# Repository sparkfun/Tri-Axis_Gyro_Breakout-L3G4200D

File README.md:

SparkFun Tri-Axis Gyro Breakout - L3G4200D
========================================

[*SparkFun Tri-Axis Gyro Breakout - L3G4200D (SEN-10612)*](https://www.sparkfun.com/products/10612)

This is a breakout board for the L3G4200D low-power three-axis angular rate sensor. 
The L3G4200D is a MEMS motion sensor and has a full scale of ±250/±500/±2000 dps and is capable of measuring rates with a user-selectable bandwidth. 

Repository Contents
-------------------

* **/Firmware** - Example code 
* **/Hardware** - Eagle design files (.brd, .sch)
* **/Production** - Production panel files (.brd)

Documentation
--------------
* **[SparkFun Fritzing repo](https://github.com/sparkfun/Fritzing_Parts)** - Fritzing diagrams for SparkFun products.
* **[SparkFun 3D Model repo](https://github.com/sparkfun/3D_Models)** - 3D models of SparkFun products. 

License Information
-------------------
This product is _**open source**_! 

The **hardware** is released under [Creative Commons ShareAlike 4.0 International](https://creativecommons.org/licenses/by-sa/4.0/).

The **code** is beerware; if you see me (or any other SparkFun employee) at the local, and you've found our code helpful, please buy us a round!

Please use, reuse, and modify these files as you see fit. Please maintain attribution to SparkFun Electronics and release anything derivative under the same license.

Distributed as-is; no warranty is given.

- Your friends at SparkFun.

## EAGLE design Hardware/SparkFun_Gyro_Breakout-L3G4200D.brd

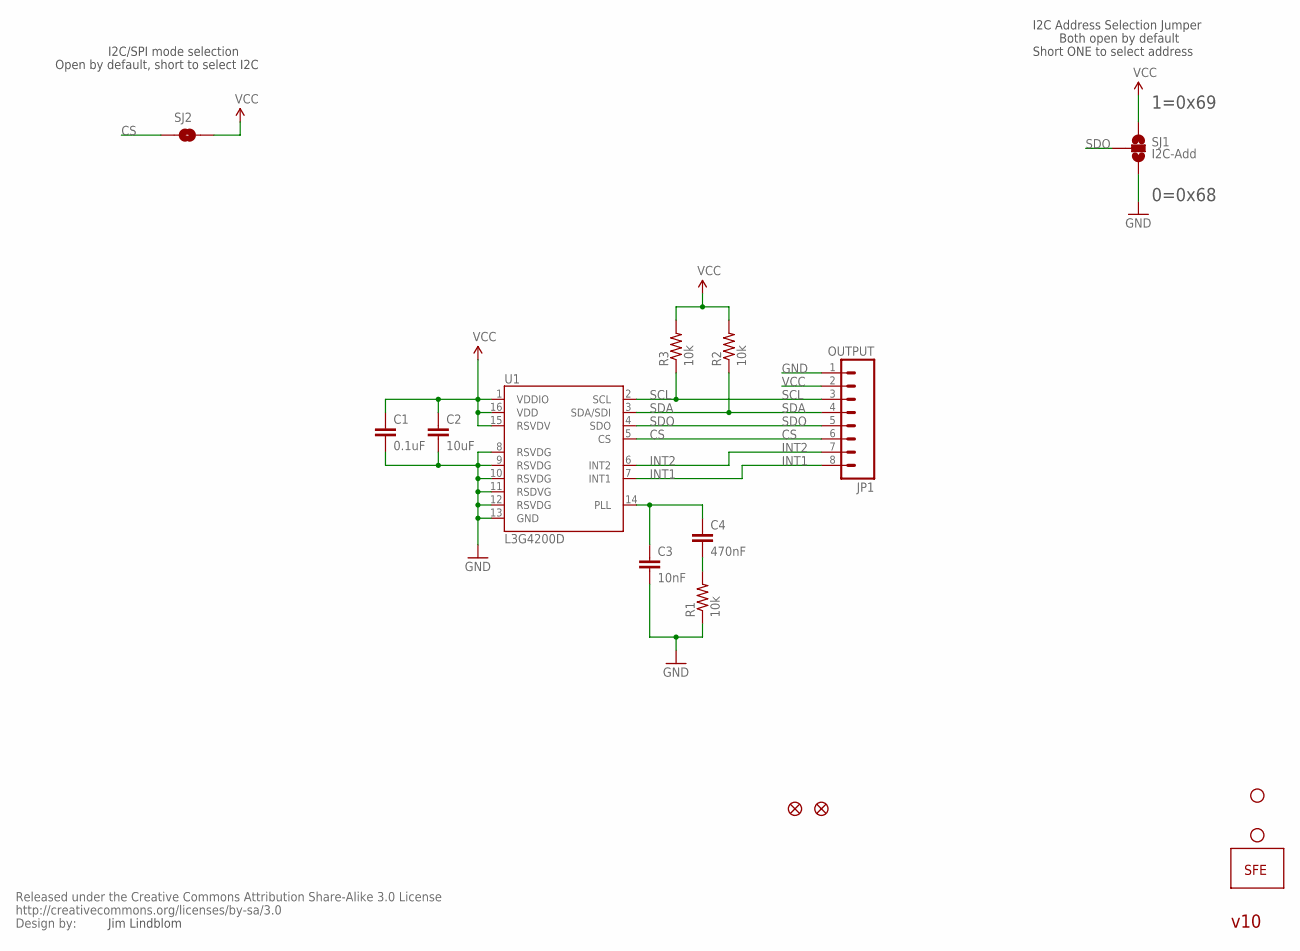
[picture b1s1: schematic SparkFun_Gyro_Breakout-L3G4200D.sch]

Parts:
C1: 0.1uF; 0402-CAP
C2: 10uF; 1206
C3: 10nF; 0402-CAP
C4: 470nF; 0402-CAP
JP1: OUTPUT; 1X08
JP2, JP3: STAND-OFF
JP4: LOGO-SFESK; SFE-LOGO-FLAME
JP5, JP6: FIDUCIAL1X2; FIDUCIAL-1X2
R1, R2, R3: 10k; 0402-RES
SJ1: I2C-Add; SJ_3
SJ2: I2C-Mode; SJ_2S-NO
U1: L3G4200D; LGA16-4X4
U$1: CREATIVE_COMMONS

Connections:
CS: JP1.6, SJ2.1, U1.5 (CS)
GND: C1.2, C2.2, C3.2, JP1.1, R1.1, SJ1.3, U1.8 (RSVDG), U1.9 (RSVDG), U1.10 (RSVDG), U1.11 (RSDVG), U1.12 (RSVDG), U1.13 (GND)
INT1: JP1.8, U1.7 (INT1)
INT2: JP1.7, U1.6 (INT2)
PLL: C3.1, C4.1, U1.14 (PLL)
PLL-2: C4.2, R1.2
SCL: JP1.3, R3.1, U1.2 (SCL)
SDA: JP1.4, R2.1, U1.3 (SDA/SDI)
SDO: JP1.5, SJ1.2, U1.4 (SDO)
VCC: C1.1, C2.1, JP1.2, R2.2, R3.2, SJ1.1, SJ2.2, U1.1 (VDDIO), U1.15 (RSVDV), U1.16 (VDD)

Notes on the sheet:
I2C Address Selection Jumper
Jim Lindblom
Both open by default
1=0x69
0=0x68
Short ONE to select address
I2C/SPI mode selection
Open by default, short to select I2C
v10

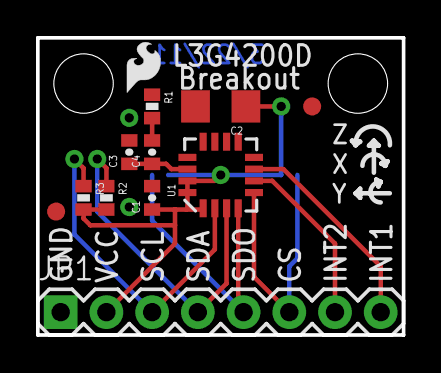
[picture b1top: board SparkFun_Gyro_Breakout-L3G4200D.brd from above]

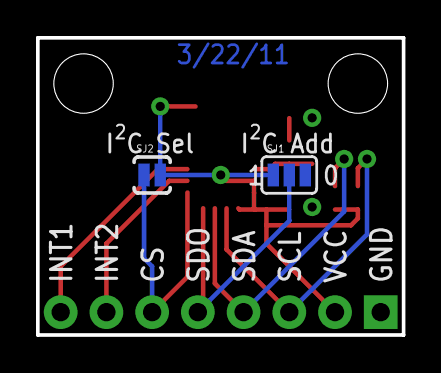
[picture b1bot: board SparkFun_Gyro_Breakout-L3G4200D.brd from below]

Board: 2 copper layers, 20.3 x 16.5 mm, 17 parts (2 on the bottom side), 10 nets.

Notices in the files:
parts and their libraries:
SparkFun: Released under the Creative Commons Attribution Share-Alike 3.0 License
SparkFun: http://creativecommons.org/licenses/by-sa/3.0
SparkFun-Aesthetics: Licensing: CC v3.0 Share-Alike You are welcome to use this library for commercial purposes.
